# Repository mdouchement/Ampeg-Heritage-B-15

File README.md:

# Ampeg HB15

This project is a custom modification of the original Ampeg Heritage B15.
You can download the schematic [HB15.pdf](HB15.pdf).

## Warnings

- Use **6L6GC** valves that support 500V at the screen
- Always checks that all capacitors are discharged
  - Even if the 470k 2W resistor shoud discharged the capacitor

## Valves

Valves used in this project:
- TAD - 6L6GCM-STR REDBASE
- Philips USA as JAN 12AT7WC (6201) [NOS military grade]
- JAN 6SL7WGT Philips               [NOS military grade]
- Shuguang 6N9P J level             [NOS military grade]

## Custom mods

- The 100K 2W resistor in parallel with the standby switch reduce all the inrush current which is better for the capacitors
- Boost switches increase the gain of the triode by adding a bypass capactor
- Enable or disable the bright capacitor (boost in 8kHz)
- Effects Loop (buffered) is built to be transparent and you can do severals things around:
  - Enable or disable the effects loop
  - Can be used as a buffered preamp out
  - Can be used as an input for a "preamp in a box"
  - Can be used as distortion stage on the cathode follower by increasing the send volume
    - *Eventually a clean boost of the preamp*
- Post Phase Inverter Master Volume (PPIMV) allowing to push the preamp while keeping the amplifier not too loud
- Negative Feedback loop for rumble fix and different voicing (see schematic)
- Midranges boost is a custom version inpired from Pignose B100V amp
- Adding a 4.7nF capacitor in series with C1 and C3 to cut sub frequencies
  - It may be a side effect by replacing all 22nF by 47nF in order to support a 5 strings bass
  - It also due to the frequency response of my PF-210HE cabinet which have a greater low frequencies response
  - 3.3nF may be better depending your cabinet (and taste)

## Tips

- Use a rubber seal inside the chassis to easily mount a APEM 644 for example
- Use teflon tape and rubber seal to insulate metalic jack plug (e.g. Switchcraft 11) from the chassis to avoid ground loops
- Avoid soldering ground on the potentiometer's cover (gound loops enabler)

## Tools

- [KiCAD](https://kicad.org)
  - https://gitlab.com/kicad/code/kicad
  - https://github.com/KiCad
- [DIYLC](http://diy-fever.com/software/diylc)
  - https://github.com/bancika/diy-layout-creator
- [LiveSPICE](https://github.com/dsharlet/LiveSPICE)
- [Micro-Cap](http://www.spectrum-soft.com/index.shtm)

## Resources

- https://ampeg.com/support/files/Schematics/
- http://www.valvewizard.co.uk/index.html
- https://www.ampbooks.com/mobile/amplifier-calculators
- http://www.guitarscience.net/tsc/info.htm (tonestack calculator)
- https://trioda.com/tools/triode.html (Loadline calculator)

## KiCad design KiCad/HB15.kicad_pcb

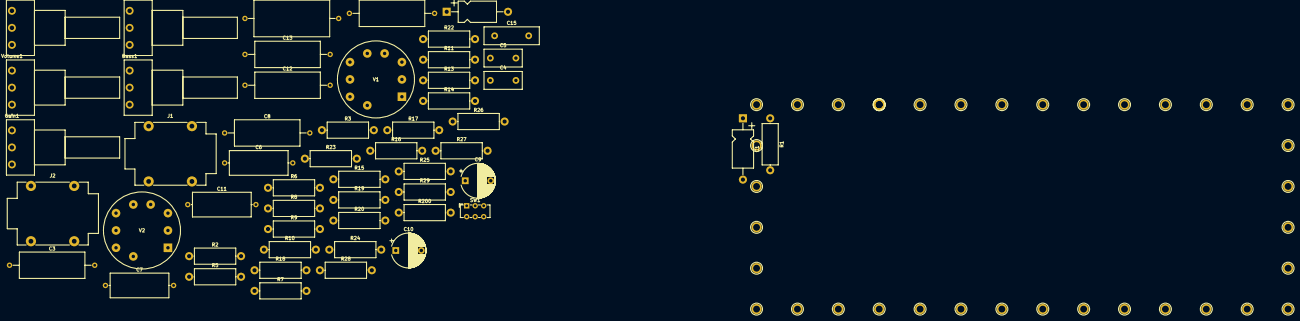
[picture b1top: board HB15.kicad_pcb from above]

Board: 2 copper layers, 53 parts (0 on the bottom side), 37 nets, no tracks yet.

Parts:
Bass1: B250K; Potentiometer_Piher_PC-16_Single_Horizontal
C1, C2: 22µF 50V; CP_Axial_L11.0mm_D6.0mm_P18.00mm_Horizontal
C3, C8, C12, C13: 100nF 400V; C_Axial_L19.0mm_D7.5mm_P25.00mm_Horizontal
C4: 47pF 1KV; C_Disc_D11.0mm_W5.0mm_P7.50mm
C5: 150pF; C_Disc_D11.0mm_W5.0mm_P7.50mm
C6, C7, C11: 47nF; C_Axial_L17.0mm_D7.0mm_P20.00mm_Horizontal
C9, C10: 10µF 250V; CP_Radial_D10.0mm_P7.50mm
C14: 220nF 400V; C_Axial_L22.0mm_D10.5mm_P27.50mm_Horizontal
C15: 1nF; C_Disc_D16.0mm_W5.0mm_P10.00mm
C200: 100nF; C_Axial_L19.0mm_D7.5mm_P25.00mm_Horizontal
Gain1: A250K; Potentiometer_Piher_PC-16_Single_Horizontal
J1: Line in; Jack_6.35mm_Neutrik_NMJ4HCD2_Horizontal
J2: Line out; Jack_6.35mm_Neutrik_NMJ4HCD2_Horizontal
Midrange1: B25K; Potentiometer_Piher_PC-16_Single_Horizontal
R1, R2, R19: 1.5K 0.5W; R_Axial_DIN0414_L11.9mm_D4.5mm_P15.24mm_Horizontal
R3, R11, R20: 100K 1W; R_Axial_DIN0414_L11.9mm_D4.5mm_P15.24mm_Horizontal
R5, R15: 68K; R_Axial_DIN0414_L11.9mm_D4.5mm_P15.24mm_Horizontal
R6: 220K; R_Axial_DIN0414_L11.9mm_D4.5mm_P15.24mm_Horizontal
R7, R13, R18, R25, R200: 1M; R_Axial_DIN0414_L11.9mm_D4.5mm_P15.24mm_Horizontal
R8, R10, R23, R28: 470K; R_Axial_DIN0414_L11.9mm_D4.5mm_P15.24mm_Horizontal
R9, R17, R22, R24, R27: 100K; R_Axial_DIN0414_L11.9mm_D4.5mm_P15.24mm_Horizontal
R14: 47K; R_Axial_DIN0414_L11.9mm_D4.5mm_P15.24mm_Horizontal
R16: 10K 1W; R_Axial_DIN0414_L11.9mm_D4.5mm_P15.24mm_Horizontal
R26: 1.5K; R_Axial_DIN0414_L11.9mm_D4.5mm_P15.24mm_Horizontal
R29: 10K; R_Axial_DIN0414_L11.9mm_D4.5mm_P15.24mm_Horizontal
SW1: On/Bypass; SW_E-Switch_EG1271_DPDT
Treble1: B250K; Potentiometer_Piher_PC-16_Single_Horizontal
V1, V2: ECC83; Valve_Noval_P
Volume1: A250K; Potentiometer_Piher_PC-16_Single_Horizontal

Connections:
GND: C1.2, C2.2, C9.2, C10.2, C15.2, Gain1.1, J1.T, J2.T, Midrange1.1, R1.2, R2.2, R7.2, R8.2, R10.2, R13.2, R18.2, R19.2, R23.2, R27.2, R28.2, R200.2, Volume1.1
unnamed: Bass1.1, C7.1, Midrange1.2, Midrange1.3
unnamed: Bass1.2, Bass1.3, C6.1, Treble1.1
unnamed: C1.1, C4.2, R1.1, V1.3
unnamed: C2.1, R2.1, V1.8
unnamed: C3.1, R6.1
unnamed: C3.2, R3.2, V1.1
unnamed: C4.1, R5.1, R7.1, V1.2
unnamed: C5.1, Treble1.3
unnamed: C5.2, R14.2, R15.1
unnamed: C6.2, C7.2, R15.2
unnamed: C8.1, R13.1, R14.1
unnamed: C8.2, R11.2, V1.6
unnamed: C9.1, R3.1, R11.1, R16.1
unnamed: C11.1, R17.1
unnamed: C11.2, Treble1.2
unnamed: C12.1, R22.1
unnamed: C12.2, R20.2, V2.1
unnamed: C13.1, R24.1
unnamed: C13.2, Volume1.2
unnamed: C14.1, R28.1, R29.1
unnamed: C14.2, R26.1, V2.8
unnamed: C15.1, R29.2, SW1.6
unnamed: C200.1, R5.2
unnamed: C200.2, R200.1, SW1.3
unnamed: Gain1.2, R9.1
unnamed: Gain1.3, R6.2, R8.1
unnamed: J1.S, SW1.2
unnamed: J2.S, SW1.5
unnamed: R9.2, R10.1, V1.7
unnamed: R17.2, R18.1, V2.2
unnamed: R19.1, V2.3
unnamed: R22.2, R23.1, Volume1.3
unnamed: R24.2, R25.1, V2.7
unnamed: R25.2, R26.2, R27.1
unnamed: SW1.1, SW1.4
VCC: C10.1, R16.2, R20.1, V2.6

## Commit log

2022-01-30 v2 before KiCad6 to rebase with the final commit
2022-01-30 KiCad6
2022-08-27 Tidy
